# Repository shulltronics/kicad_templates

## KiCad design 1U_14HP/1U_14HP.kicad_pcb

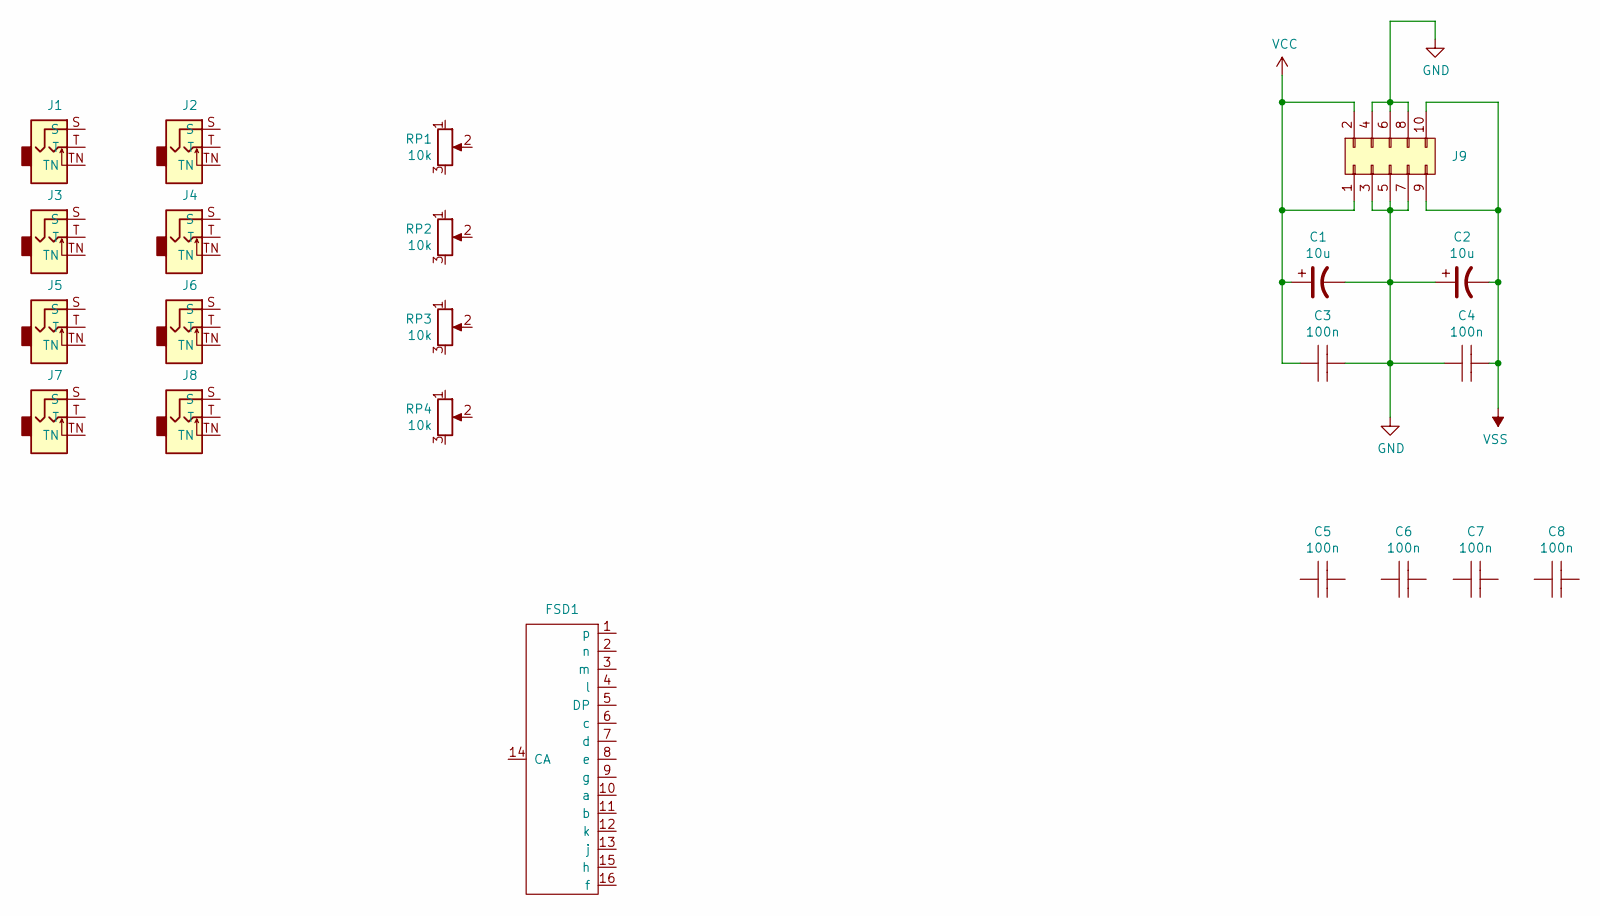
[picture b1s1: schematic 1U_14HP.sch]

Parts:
C1, C2: 3088_Capacitor_10u_50V_SMD
C3, C4, C5, C6, C7, C8: 3089_Capacitor_100n_16V_SMD; C_0402_HandSolder
FSD1: 3023_FSD; 3023_14seg_Display
J1, J2, J3, J4, J5, J6, J7, J8: 3085_MiniJack_Thonk_Vert
J9: 3086_Connector_Eurorack_Power; 3086_SMD_Eurorack_Power
RP1, RP2, RP3, RP4: 3087_Potentiometer_10k_Linear; 3087_Potentiometer_10k

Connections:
GND: C1.2, C2.1, C3.2, C4.1, J9.3, J9.4, J9.5, J9.6, J9.7, J9.8
VCC: C1.1, C3.1, J9.1, J9.2
VSS: C2.2, C4.2, J9.9, J9.10

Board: 4 copper layers, 22 parts (9 on the bottom side), 3 nets, no tracks yet.

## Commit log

2021-11-23 First template
